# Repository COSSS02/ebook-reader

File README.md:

# E-book Reader

This is my implementation of an E-book Reader, made entirely in Autodesk Fusion.

## Device

## Exploded View

## PCB

## Block Diagram

## ESP32-C6 Pin Connections

### E-Paper Display
- MOSI --> GPIO4
- SCK --> GPIO5
- RESET --> GPIO15
- BUSY --> GPIO16
- CS --> GPIO17
- DC --> GPIO18

### SD Card
- CLK --> GPIO6
- CMD --> GPIO7
- DATA0 --> GPIO8
- DATA1 --> GPIO9
- DATA2 --> GPIO10
- DATA3 --> GPIO11

### NOR Flash Memory
- MOSI --> GPIO4
- MISO --> GPIO3
- CLK --> GPIO5
- CS --> GPIO2

### Temp/RH Sensor
- SDA --> GPIO19
- SCL --> GPIO20

### RTC Module
- SDA --> GPIO19
- SCL --> GPIO20

### Qwiic / Stemma QT
- SDA --> GPIO19
- SCL --> GPIO20

### Battery Charge Level
- SDA --> GPIO19
- SCL --> GPIO20

### Buttons
- Reset --> GPIO0
- Boot --> GPIO1

## Bill of Materials

| Component             | Datasheet                        |
|-----------------------|----------------------------------|
| ESP32-C6-WROOM-1-N8   | [Mouser](https://mou.sr/42swLfH) |
| FH34SRJ-24S-0.5SH     | [Mouser](https://mou.sr/43Cr53R) |
| XC6220A331MR-G        | [Mouser](https://mou.sr/4ieKgVa) |
| MAX17048G+T10         | [Mouser](https://mou.sr/3FWR5wY) |
| W25Q512JVEIQ          | [Mouser](https://mou.sr/42vsB6J) |
| USB4110-GF-A          | [Mouser](https://mou.sr/4iUMo5l) |
| USBLC6-2SC6Y          | [Mouser](https://mou.sr/42lyiTK) |
| DS3231SN#             | [Mouser](https://mou.sr/42jhNr4) |
| BME680                | [Mouser](https://mou.sr/42kgEzJ) |
| PFMF.050.2            | [Mouser](https://mou.sr/4cjORnD) |
| BD5229G-TR            | [Mouser](https://mou.sr/3EckiDF) |
| MBR0530-TP            | [Mouser](https://mou.sr/4i9Ddgn) |
| DMG2305UX-7           | [Mouser](https://mou.sr/4ci24gy) |
| PGB1010603MR          | [Mouser](https://mou.sr/3Yg9sDe) |
| Adafruit 4208         | [Mouser](https://mou.sr/4lcY19f) |
| SD0805S020S1R0        | [Mouser](https://mou.sr/4cljSYj) |
| SI1308EDL-T1-GE3      | [Mouser](https://mou.sr/4lj7JXH) |
| MCP73831-2ACI/MC      | [Mouser](https://mou.sr/3XJhnsM) |

## Hardware Description

### Main Controller

    ESP32-C6-WROOM-1-N8: RISC-V based microcontroller with WiFi 6 and Bluetooth 5.0 LE

    Operating Voltage: 3.3V

    Clock Speed: 160MHz

### Memory Configuration

    External NOR Flash: W25Q512JVEIQ (64MB capacity)

    Interface: SPI (Serial Peripheral Interface)

### Power Management System

    Primary Regulator: XC6220A331MR-G (3.3V LDO)

    Battery Charger: MCP73831 (Li-Po charging controller)

    Fuel Gauge: MAX17048G+T10 (Battery monitoring IC)

    Power Path Protection:

        MBR0530 Schottky diodes (x3)

        SI1308EDL-T1-GE3 MOSFET

### Display System

    E-Paper Display Interface: Dedicated header with ESD protection

    Display Driver Circuit: Custom EPD power management

    Control Signals:

        EPD_RST (Reset)

        EPD_BUSY (Status)

        EPD_DC (Data/Command)

        EPD_CS (Chip Select)

### Environmental Sensing

    BME688: Integrated environmental sensor with:

        Temperature

        Humidity

        Barometric pressure

        Air quality (VOC detection)

    Interface: I2C (Qwiic/Stemma QT compatible)

### Real-Time Clock

    DS3231SN: High-precision RTC with:

        ±2ppm accuracy

        Integrated temperature compensation

        Battery backup support

        Square wave/interrupt output

### Connectivity Interfaces USB

    Type-C Connector: USB 2.0 compliant

    ESD Protection: USBLC6-2SC6Y

    Data Lines:

        USB_D+

        USB_D-

### Expansion Ports

    Qwiic/Stemma QT: 4-pin I2C connector

    SD Card Slot: Supports standard SD cards

        Interface: SPI mode

        Detection switch included

### Debugging Interfaces

    Test Points: 17 accessible test points

### Power Specifications

    Input Voltage: 5V via USB-C

    Battery Voltage: 3.7V Li-Po

    Power Tree:

        Primary 3.3V rail for digital components

        Dedicated 3.3V rail for display

        RTC backup power circuit

### Mechanical Interfaces

    24-pin FH34SRJ Connector: Display interface

    Tactile Buttons:

        Reset button

        Boot/IO button

        Custom function buttons

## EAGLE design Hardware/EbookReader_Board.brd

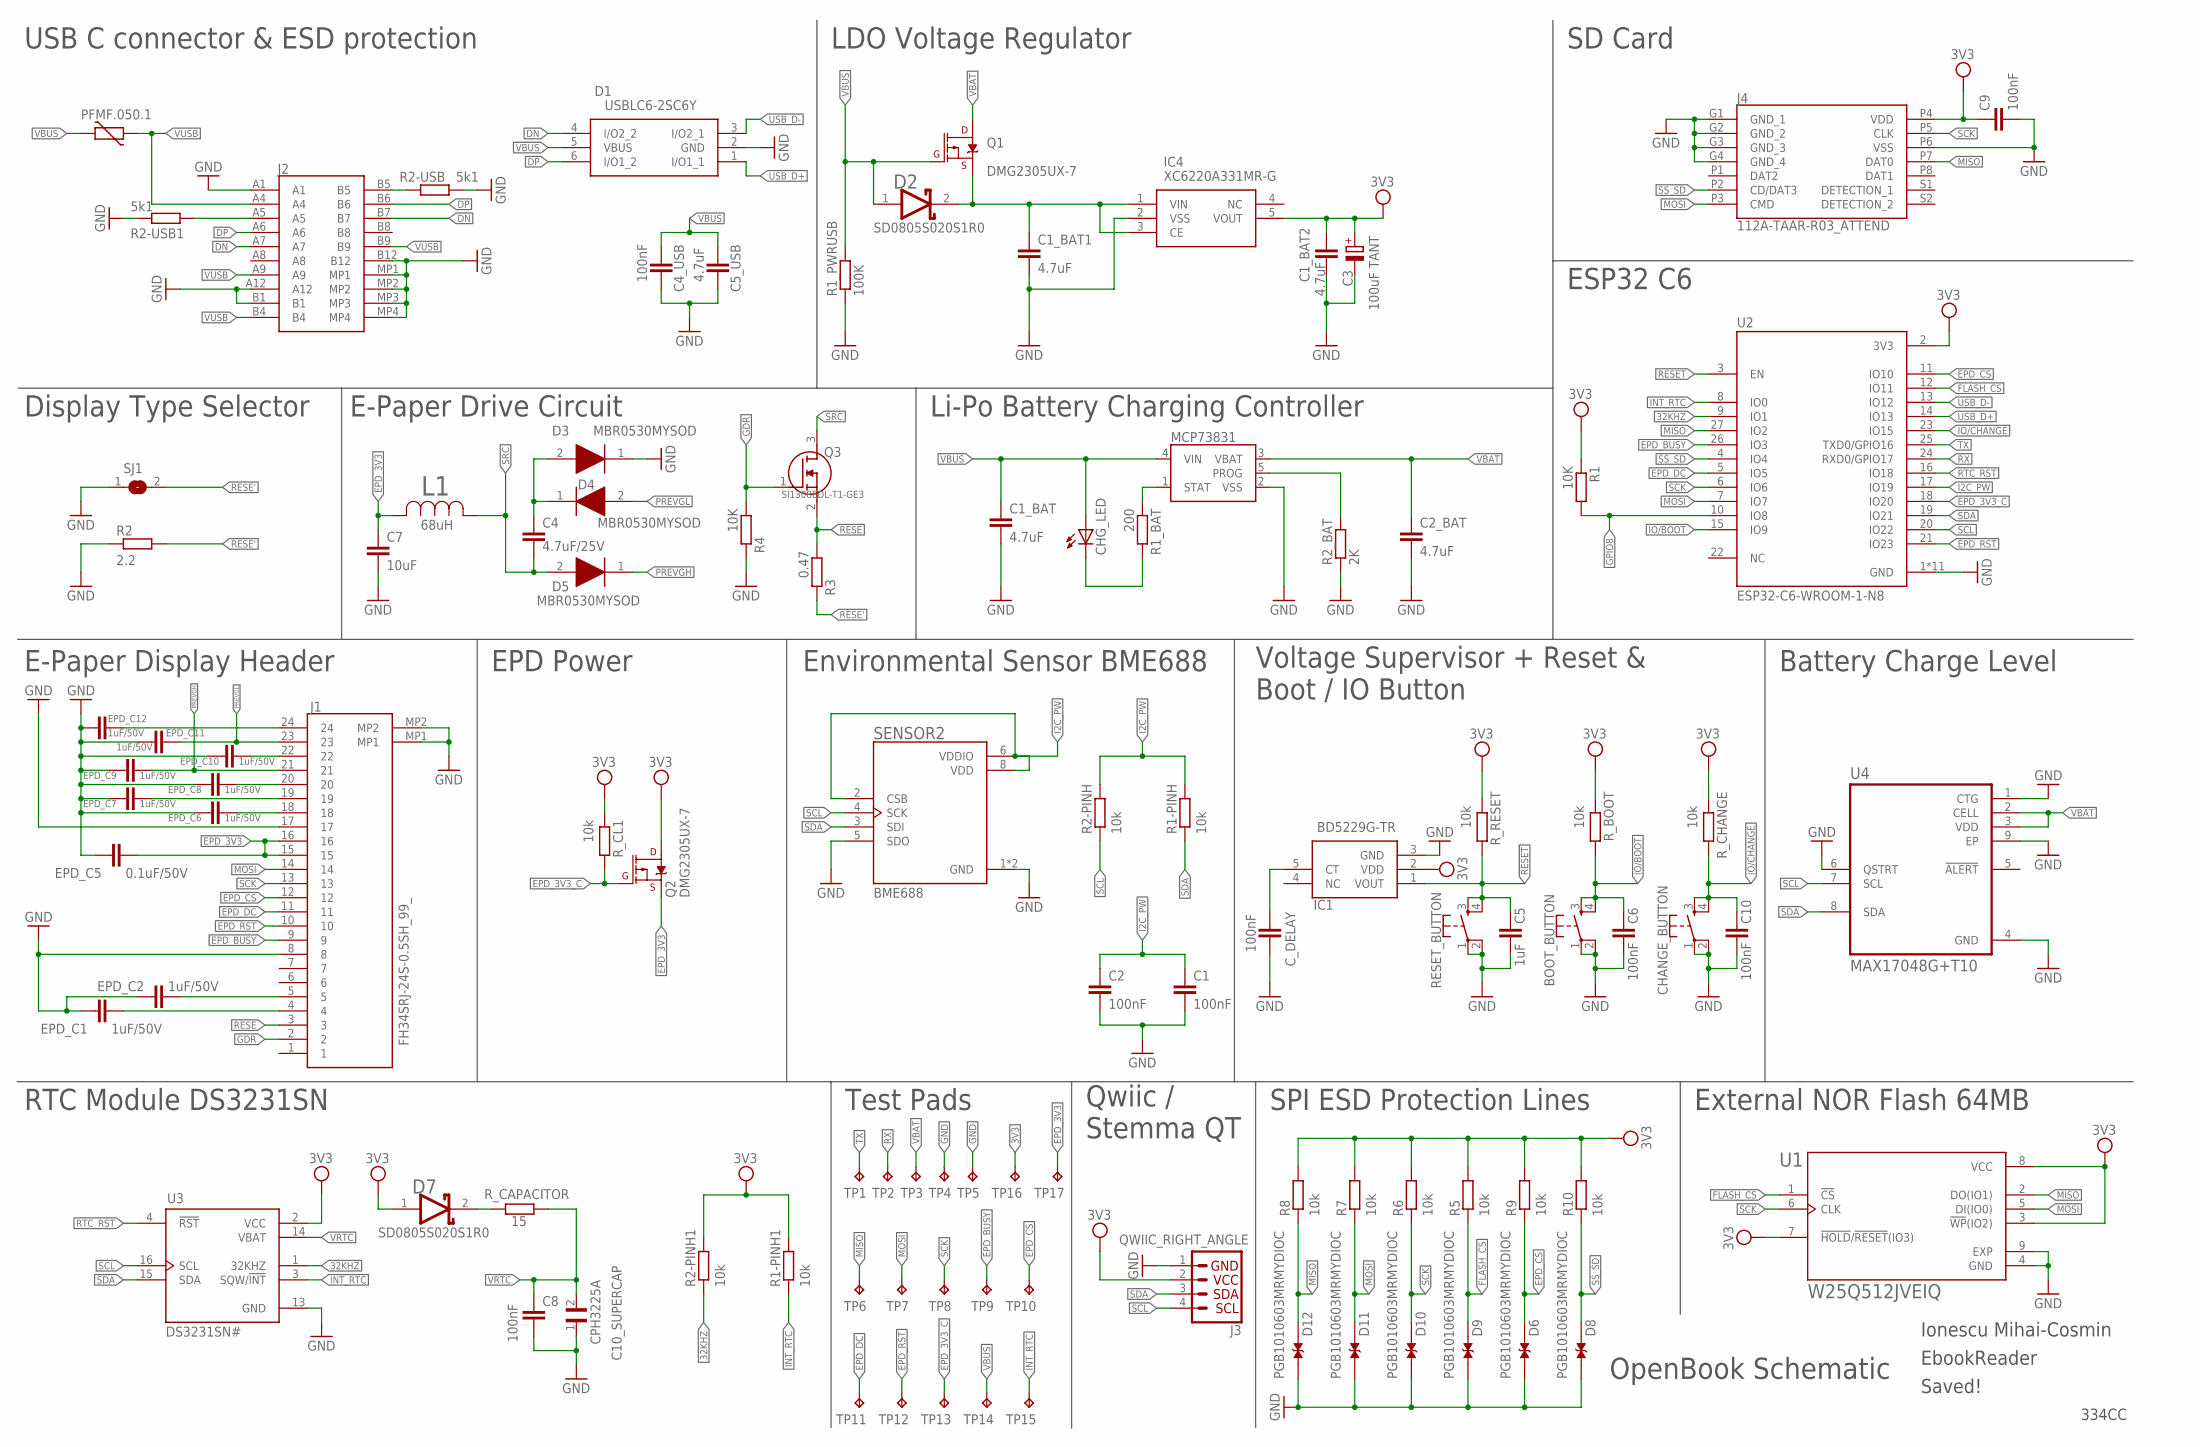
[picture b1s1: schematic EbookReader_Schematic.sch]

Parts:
BOOT_BUTTON: BUTTON_CUSYOMV1FINAL_BUTT; MYBUTTON
C1, C2, C4_USB, C6, C8, C9, C10: 100nF; EAGLE-LTSPICE_C0402
C1_BAT, C1_BAT1, C1_BAT2, C2_BAT, C5_USB: 4.7uF; EAGLE-LTSPICE_C0402
C3: 100uF TANT; RCL_CT3528
C4: 4.7uF/25V; EAGLE-LTSPICE_C0402
C5: 1uF; EAGLE-LTSPICE_C0402
C7: 10uF; EAGLE-LTSPICE_C0402
C10_SUPERCAP: CPH3225A; CAPCP3225X100N
CHANGE_BUTTON: BUTTON_CUSYOMV1FINAL_BUTT; MYBUTTON
CHG_LED: ADAFRUIT_LEDCHIP-LED0603; ADAFRUIT_CHIP-LED0603
C_DELAY: 100nF; EAGLE-LTSPICE_C0402
D1: USBLC6-2SC6Y; SOT95P280X145-6N
D2, D7: ESP32_WROVER_AVX---SD0805S020S1R0_AVX_SD0805S020S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; ESP32_WROVER_AVX---SD0805S020S1R0_AVX_SD0805S020S1R0_0
D3, D4, D5: MBR0530MYSOD; SOD3716X135N
D6, D8, D9, D10, D11, D12: PGB1010603MRMYDIOC; DIOC1608X36N
EPD_C1, EPD_C2, EPD_C6, EPD_C7, EPD_C8, EPD_C9, EPD_C10, EPD_C11, EPD_C12: 1uF/50V; EAGLE-LTSPICE_C0402
EPD_C5: 0.1uF/50V; EAGLE-LTSPICE_C0402
IC1: BD5229G-TR; SOT95P280X125-5N
IC4: XC6220A331MR-G; SOT95P280X120-5N
J1: FH34SRJ-24S-0.5SH_99_; FH34SRJ24S05SH99
J2: SAMACSYS_PARTS_USB4110-GF-A; SAMACSYS_PARTS_USB4110GFA
J3: QWIIC_RIGHT_ANGLE; JST04_1MM_RA
J4: 112A-TAAR-R03_ATTEND; 112ATAARR03ATTEND
L1: 744043680IND_4828-WE-TPC_WRE; IND_4828-WE-TPC_WRE
MCP73831: ESP32_WROVER_SPARKFUN-IC-POWER_MCP73831; ESP32_WROVER_SPARKFUN-IC-POWER_SOT23-5
PFMF.050.1: ESP32C6_VARISTORCN1812; ESP32C6_VARISTOR_CT/CN1812
Q1, Q2: 20V/4.2A/52mΩ/1.4W; ESP32_WROVER_SPARKFUN-DISCRETESEMI_SOT23-3
Q3: SI1308EDL-T1-GE3; SOT65P210X110-3N
R1, R4: 10K; ESP32_WROVER_EAGLE-LTSPICE_R0402
R1-PINH, R1-PINH1, R2-PINH, R2-PINH1, R5, R6, R7, R8, R9, R10: 10k; ESP32_WROVER_EAGLE-LTSPICE_R0402
R1_BAT: 200; ESP32_WROVER_EAGLE-LTSPICE_R0402
R1_PWRUSB: 100K; ESP32_WROVER_EAGLE-LTSPICE_R0402
R2: 2.2; ESP32_WROVER_EAGLE-LTSPICE_R0402
R2-USB, R2-USB1: 5k1; ESP32_WROVER_EAGLE-LTSPICE_R0402
R2_BAT: 2K; ESP32_WROVER_EAGLE-LTSPICE_R0402
R3: 0.47; ESP32_WROVER_EAGLE-LTSPICE_R0402
RESET_BUTTON: BUTTON_CUSYOMV1FINAL_BUTT; MYBUTTON
R_BOOT: 10k; ESP32_WROVER_EAGLE-LTSPICE_R0402
R_CAPACITOR: 15; ESP32_WROVER_EAGLE-LTSPICE_R0402
R_CHANGE: 10k; ESP32_WROVER_EAGLE-LTSPICE_R0402
R_CL1: 10k; ESP32_WROVER_EAGLE-LTSPICE_R0402
R_RESET: 10k; ESP32_WROVER_EAGLE-LTSPICE_R0402
SENSOR2: ESP32_WROVER_BME680_BME680; ESP32_WROVER_BME680_PSON80P300X300X100-8N
SJ1: SJ
TP1, TP2, TP3, TP4, TP5, TP6, TP7, TP8, TP9, TP10, TP11, TP12, TP13, TP14, TP15, TP16, TP17: TP; TP20R
U1: W25Q512JVEIQ; SON127P600X800X80-9N
U2: ESP32-C6-WROOM-1-N8; XCVR_ESP32-C6-WROOM-1-N8
U3: DS3231SN#; SOIC127P1032X265-16N
U4: MAX17048G+T10; SON50P200X200X80-9N

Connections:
3V3: C1_BAT2.1, C3.+, C9.1, D7.1 (ANODE), IC1.2 (VDD), IC4.5 (VOUT), J3.2, J4.P4 (VDD), Q2.1 (D), R1.1, R1-PINH1.2, R2-PINH1.2, R5.2, R6.2, R7.2, R8.2, R9.2, R10.2, R_BOOT.1, R_CHANGE.1, R_CL1.1, R_RESET.1, TP16.TP, U1.3 (!WP!(IO2)), U1.7 (!HOLD!/!RESET!(IO3)), U1.8 (VCC), U2.2 (3V3), U3.2 (VCC)
32KHZ: R2-PINH1.1, U2.9 (IO1), U3.1 (32KHZ)
DN: D1.4 (I/O2_2), J2.A7, J2.B7
DP: D1.6 (I/O1_2), J2.A6, J2.B6
EPD_3V3: C7.1, EPD_C5.1, J1.15, J1.16, L1.2, Q2.3 (S), TP17.TP
EPD_3V3_C: Q2.2 (G), R_CL1.2, TP13.TP, U2.18 (IO20)
EPD_BUSY: J1.9, TP9.TP, U2.26 (IO3)
EPD_CS: D6.2, J1.12, R9.1, TP10.TP, U2.11 (IO10)
EPD_DC: J1.11, TP11.TP, U2.5 (IO5)
EPD_RST: J1.10, TP12.TP, U2.21 (IO23)
FLASH_CS: D9.2, R5.1, U1.1 (!CS), U2.12 (IO11)
GDR: J1.2, Q3.1 (G), R4.1
GND: BOOT_BUTTON.1, BOOT_BUTTON.2, C1.2, C1_BAT.2, C1_BAT1.2, C1_BAT2.2, C2.2, C2_BAT.2, C3.-, C4_USB.2, C5.2, C5_USB.2, C6.2, C7.2, C8.2, C9.2, C10.2, C10_SUPERCAP.1, CHANGE_BUTTON.1, CHANGE_BUTTON.2, C_DELAY.2, D1.2 (GND), D3.1 (K), D6.1, D8.1, D9.1, D10.1, D11.1, D12.1, EPD_C1.2, EPD_C2.2, EPD_C5.2, EPD_C6.2, EPD_C7.2, EPD_C8.2, EPD_C9.2, EPD_C10.2, EPD_C11.2, EPD_C12.2, IC1.3 (GND), IC4.2 (VSS), J1.8, J1.17, J1.MP1, J1.MP2, J2.A1, J2.A12, J2.B1, J2.B12, J2.MP1, J2.MP2, J2.MP3, J2.MP4, J3.1, J4.G1 (GND_1), J4.G2 (GND_2), J4.G3 (GND_3), J4.G4 (GND_4), J4.P6 (VSS), MCP73831.2 (VSS), R1_PWRUSB.1, R2.1, R2-USB.2, R2-USB1.1, R2_BAT.1, R4.2, RESET_BUTTON.1, RESET_BUTTON.2, SENSOR2.1 (GND), SENSOR2.5 (SDO), SENSOR2.7 (GND), SJ1.1, TP4.TP, TP5.TP, U1.4 (GND), U1.9 (EXP), U2.1 (GND), U2.28 (GND), U2.29_1 (GND), U2.29_2 (GND), U2.29_3 (GND), U2.29_4 (GND), U2.29_5 (GND), U2.29_6 (GND), U2.29_7 (GND), U2.29_8 (GND), U2.29_9 (GND), U3.13 (GND), U4.1 (CTG), U4.4 (GND), U4.6 (QSTRT), U4.9 (EP)
GPIO8: R1.2, U2.10 (IO8)
I2C_PW: C1.1, C2.1, R1-PINH.2, R2-PINH.2, SENSOR2.2 (CSB), SENSOR2.6 (VDDIO), SENSOR2.8 (VDD), U2.17 (IO19)
INT_RTC: R1-PINH1.1, TP15.TP, U2.8 (IO0), U3.3 (SQW/!INT)
IO/BOOT: BOOT_BUTTON.3, BOOT_BUTTON.4, C6.1, R_BOOT.2, U2.15 (IO9)
IO/CHANGE: C10.1, CHANGE_BUTTON.3, CHANGE_BUTTON.4, R_CHANGE.2, U2.23 (IO15)
MISO: D12.2, J4.P7 (DAT0), R8.1, TP6.TP, U1.2 (DO(IO1)), U2.27 (IO2)
MOSI: D11.2, J1.14, J4.P3 (CMD), R7.1, TP7.TP, U1.5 (DI(IO0)), U2.7 (IO7)
unnamed: MCP73831.1 (STAT), R1_BAT.1
unnamed: J2.A5, R2-USB1.2
unnamed: J2.B5, R2-USB.1
unnamed: C1_BAT1.1, D2.2 (CATHODE), IC4.1 (VIN), IC4.3 (CE), Q1.3 (S)
unnamed: EPD_C2.1, J1.5
unnamed: EPD_C1.1, J1.4
unnamed: EPD_C6.1, J1.18
unnamed: EPD_C7.1, J1.19
unnamed: EPD_C8.1, J1.20
unnamed: EPD_C10.1, J1.22
unnamed: EPD_C12.1, J1.24
unnamed: CHG_LED.C, R1_BAT.2
unnamed: D7.2 (CATHODE), R_CAPACITOR.2
unnamed: MCP73831.5 (PROG), R2_BAT.2
unnamed: C4.1, D3.2 (A), D4.1 (K)
unnamed: C_DELAY.1, IC1.5 (CT)
PREVGH: D5.1 (K), EPD_C9.1, J1.21
PREVGL: D4.2 (A), EPD_C11.1, J1.23
RESE: J1.3, Q3.2 (S), R3.1
RESE': R2.2, R3.2, SJ1.2
RESET: C5.1, IC1.1 (VOUT), RESET_BUTTON.3, RESET_BUTTON.4, R_RESET.2, U2.3 (EN)
RTC_RST: U2.16 (IO18), U3.4 (!RST)
RX: TP2.TP, U2.24 (RXD0/GPIO17)
SCK: D10.2, J1.13, J4.P5 (CLK), R6.1, TP8.TP, U1.6 (CLK), U2.6 (IO6)
SCL: J3.4, R2-PINH.1, SENSOR2.4 (SCK), U2.20 (IO22), U3.16 (SCL), U4.7 (SCL)
SDA: J3.3, R1-PINH.1, SENSOR2.3 (SDI), U2.19 (IO21), U3.15 (SDA), U4.8 (SDA)
SRC: C4.2, D5.2 (A), L1.1, Q3.3 (D)
SS_SD: D8.2, J4.P2 (CD/DAT3), R10.1, U2.4 (IO4)
TX: TP1.TP, U2.25 (TXD0/GPIO16)
USB_D+: D1.1 (I/O1_1), U2.14 (IO13)
USB_D-: D1.3 (I/O2_1), U2.13 (IO12)
VBAT: C2_BAT.1, MCP73831.3 (VBAT), Q1.1 (D), TP3.TP, U4.2 (CELL), U4.3 (VDD)
VBUS: C1_BAT.1, C4_USB.1, C5_USB.1, CHG_LED.A, D1.5 (VBUS), D2.1 (ANODE), MCP73831.4 (VIN), PFMF.050.1.2, Q1.2 (G), R1_PWRUSB.2, TP14.TP
VRTC: C8.1, C10_SUPERCAP.2, R_CAPACITOR.1, U3.14 (VBAT)
VUSB: J2.A4, J2.A9, J2.B4, J2.B9, PFMF.050.1.1

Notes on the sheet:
USB C connector & ESD protection
LDO Voltage Regulator
SD Card
Display Type Selector
E-Paper Drive Circuit
Li-Po Battery Charging Controller
ESP32 C6
E-Paper Display Header
EPD Power
Environmental Sensor BME688
Voltage Supervisor + Reset & Boot / IO Button
Battery Charge Level
RTC Module DS3231SN
Test Pads
Qwiic / Stemma QT
SPI ESD Protection Lines
External NOR Flash 64MB
OpenBook Schematic
Ionescu Mihai-Cosmin
EbookReader
Saved!
334CC

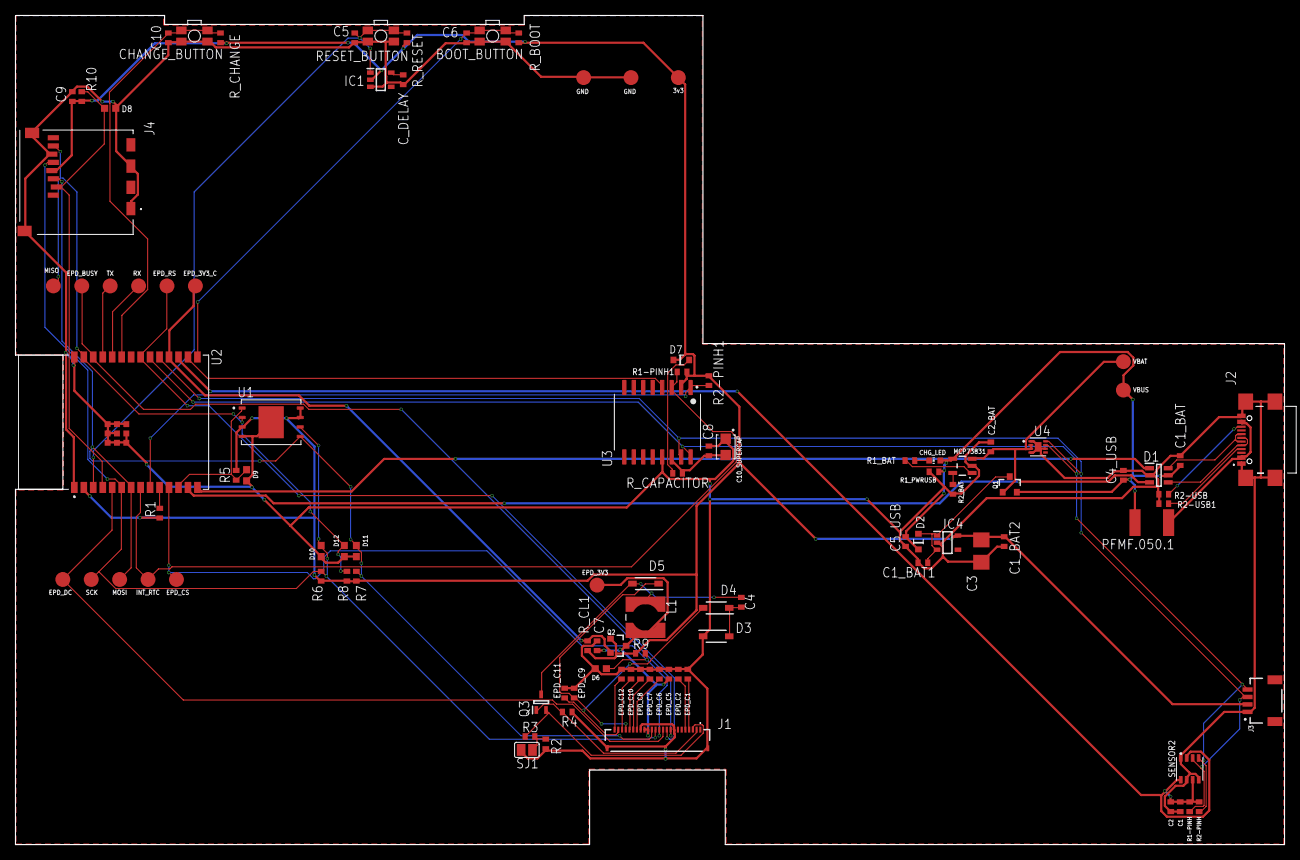
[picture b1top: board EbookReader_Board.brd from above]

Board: 2 copper layers, 170.2 x 111.2 mm, 103 parts (0 on the bottom side), 55 nets.

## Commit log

2025-04-05 Added Hardware
2025-04-05 Mechanical
2025-04-05 Added Manufacturing
2025-04-05 Added Images
2025-04-05 AddLICENSE
2025-04-05 Added README
2025-04-06 Added Block Diagram
2025-04-11 Added Images for Exploded View
2025-04-11 Deleted old pdf of exploded view
2025-04-11 Added Exploded View .step file
2025-04-11 Fixed Board and 3D Model Issues
2025-04-11 Added exploded view image in README
2025-04-11 Fixed Issues detected during the DVT phase

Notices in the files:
parts and their libraries:
COPYRIGHT: Copyright (C) 2024 Ultra Librarian. All rights reserved.
